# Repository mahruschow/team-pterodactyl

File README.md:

# Team PTERODACTYL

Working files for the UMD near-space PTERODACTYL sensor-board redesign. The current board is an imported **v3.8 v11 baseline**, not a completed next-launch design or a fabrication release.

## Team handoff and planning

For a quick picture of progress and what's left, read [docs/REMAINING_WORK.md](docs/REMAINING_WORK.md). Start with [docs/README.md](docs/README.md) for the shared planning directory, then [current status and resume steps](docs/CURRENT_STATUS.md). The directory includes requirements, the development plan, session notes, the supplied parts workbook and native KiCad validation evidence so teammates can continue without the previous chat.

Step 3 now includes a project-local `Pterodactyl_Modules` library with draft BNO055 #2472/MS8607 #4716 carrier footprints with matching symbols, a Teensy SSW carrier, and an unassigned GPS #5440 logical symbol, plus documented connector/mounting proposals. They are not assigned to the main circuit. See [the footprint review](docs/FOOTPRINT_REVIEW.md) for pin mapping, validation and outstanding physical-fit requirements.

Step 5 adds a separate **draft v4 schematic** in `Native_KiCad_v4/`, built from the documented connection map and power architecture. It passes ERC with 0 violations and matches an independent net list, but it is not yet team-reviewed. Step 7 adds a placed (not yet routed) v4 PCB in the same project; see [the draft layout](docs/PCB_LAYOUT_V4.md). See [the power architecture and schematic plan](docs/POWER_ARCHITECTURE.md).

## Open the design

Use KiCad 10 to open `Native_KiCad_v11/PTERODACTYL_v3.8_v11.kicad_pro`. The project contains a native KiCad schematic, PCB, imported symbol and footprint libraries, and project-local library tables. These files were converted from the supplied Autodesk Fusion/Eagle source; component choices and connectivity still need engineering review.

| Folder or file | Purpose |
|---|---|
| `Native_KiCad_v11/` | Editable KiCad project and the saved October 7, 2026 PCB DRC report |
| `Native_KiCad_v4/` | Draft v4 project: schematic (Step 5) and placed, unrouted PCB (Step 7); see docs/PCB_LAYOUT_V4.md |
| `KiCad_import/` | Eagle XML schematic and board pair prepared for KiCad's Eagle importer |
| `Original_Fusion_source/` | Supplied editable `.f3z`, `.sch`, and `.brd` files for comparison |
| `Firmware_v4/` | Draft v4 logger firmware (Step 6); compiles for Teensy 4.1, not yet hardware-tested |
| `Firmware_reference/` | Original v19 and v19.1 firmware archives from the supplied package; not validated for this redesign |
| `Reference_Gerbers_v12_DO_NOT_ORDER/` | Historical Gerbers for revision comparison only |
| `PTERODACTYL_V3.8_Setup_reference.pdf` | Original setup guide from the supplied package |
| `CUSTOM_BOARD_BRIEF.md` | Sensor goals and decisions still to make |

## Current state

The imported PCB has approximately 97.79 × 97.79 mm outer dimensions, four copper layers, 39 footprints, 417 tracks, and two refilled copper zones. It uses a Teensy 4.1 baseline. A fresh KiCad 10.0.7 audit on October 18, 2026 reproduced **11 PCB DRC errors, 428 warnings, and 0 unconnected items**. Schematic ERC reported **33 errors and 10 warnings**, with **52 additional schematic/PCB parity warnings**. These findings remain unresolved. See the [validation report](docs/validation/2026-10-18/VALIDATION_SUMMARY.md) for triage and check limitations, and the [development plan](docs/DEVELOPMENT_PLAN.md) for next steps. The symbols, pin mapping, power architecture and exact module footprints still require engineering review.

The supplied Gerbers say v3.8 **v12** while the editable Fusion source says v3.8 **v11**; the Gerber job metadata also contains a v3.7 identifier. Reconcile those revisions before using any prior files for fabrication.

## Next-launch work

The intended board should log gyroscope, accelerometer, orientation, GPS, pressure, humidity, temperature, and derived altitude data. The working selection is Teensy 4.1 with Adafruit BNO055 2472, MS8607 4716 and PA1616D GPS 5440. The lead has specified no telemetry: record onboard to microSD for analysis after recovery. Saadat selected the core logger with power control, status LEDs and supply monitoring; OLED, remote probes, alternative IMU, heater and servos are outside this scope. Component placement must address interference. Battery/runtime, quantitative performance, enclosure/environment, exact control workflow and manufacturer constraints remain open. See `CUSTOM_BOARD_BRIEF.md` and the [version-one requirements draft](docs/V1_REQUIREMENTS.md), which distinguishes the selected baseline from proposed behavior and open decisions.

Before fabrication: agree on the requirements and reference revision; review the schematic and all footprints against component datasheets; check power, pin mapping, routing, and board dimensions; resolve DRC/ERC failures; generate fresh Gerbers and drill files from the approved KiCad board; inspect them in a Gerber viewer; and obtain a hardware review and prototype test.

## Collaborating

Clone this private repository, open the `.kicad_pro` file, and commit changes on a branch. Keep the KiCad project, schematic, PCB, and local libraries together. Do not commit editor lock files or local UI settings. Explain changes to connectors, sensors, pin mapping, and power in the commit or pull request so they can be checked against the schematic and firmware.

**Do not send the reference Gerbers or this imported baseline directly to a manufacturer.**

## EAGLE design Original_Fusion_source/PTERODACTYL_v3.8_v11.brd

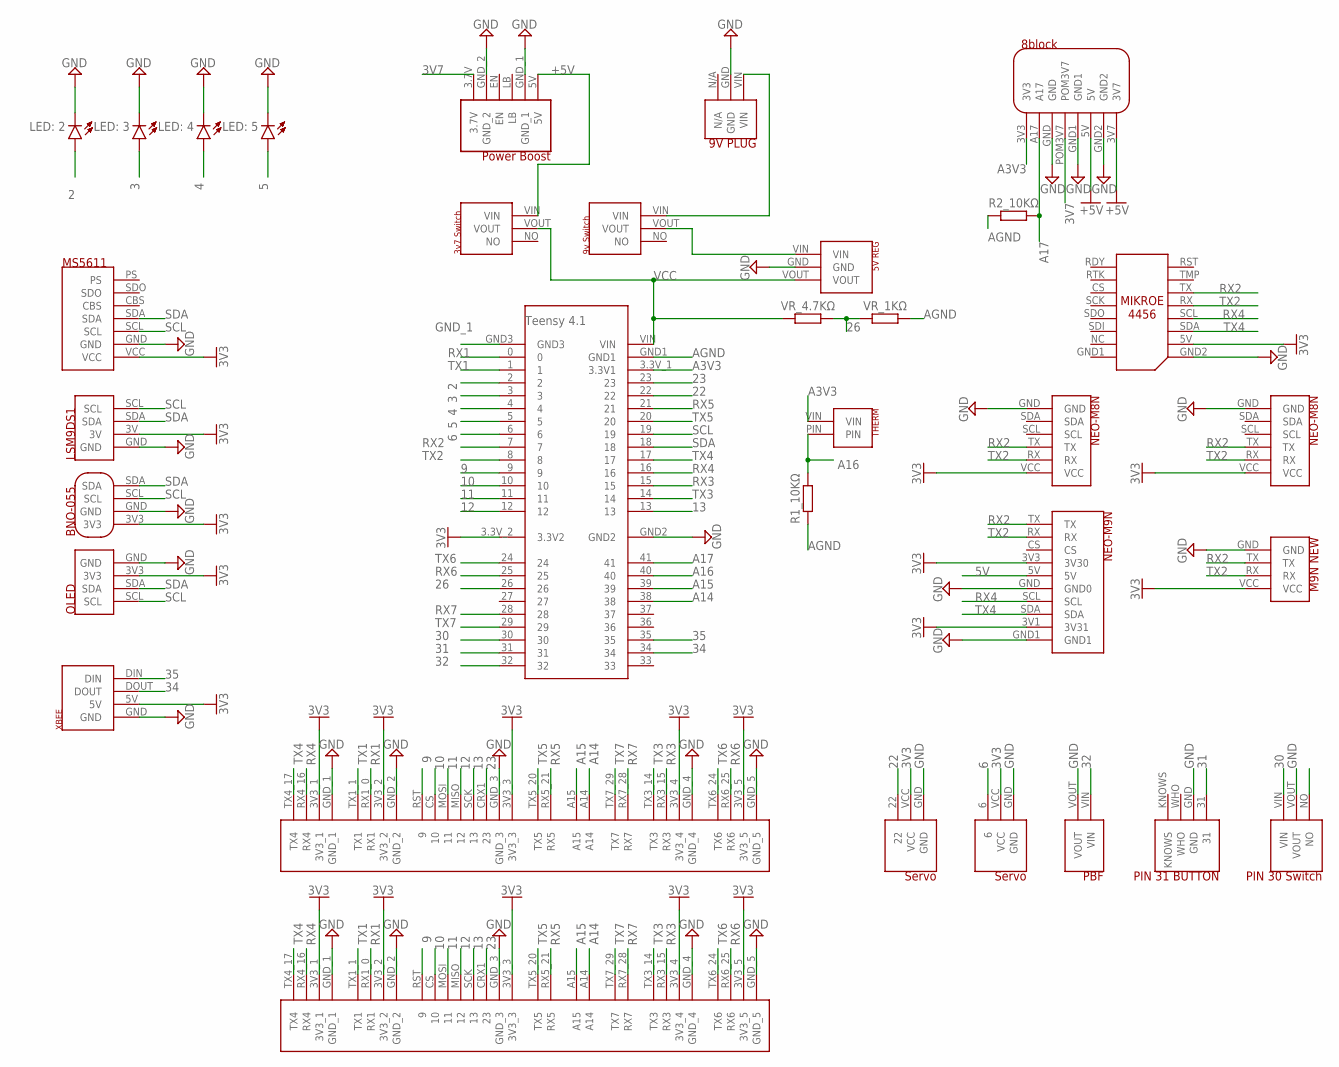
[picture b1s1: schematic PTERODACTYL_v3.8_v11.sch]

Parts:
D1: LED: 3; LEDRD254W60D565H860B_W
D2: LED: 4; LEDRD254W60D565H860B
D3: LED: 5; LEDRD254W60D565H860B_B
D4: LED: 2; LEDRD254W60D565H860B_Y
R1_10KΩ, R2_10KΩ: R_AXIAL-11.7MM-PITCH; RESAD1176W63L850D250B
U$1: FEMALE_HEADERS_V1.3
U$2: TERMINAL_BLOCK_V1.3
U$3: TEENSY41_SIMPLE
U$4: PT8BLOCK; PTERODACTYL8BLOCK
U$5: 5VREG
U$6: 3V7SWITCH
U$7: 9VSWITCH
U$8: 9VPLUG
U$9: OLED_SIMPLE
U$10: LSM9DS1_SIMPLE
U$11: MS5611
U$12: UBLOXM8NTERMINAL
U$13: UBLOXM8NSIMPLE
U$14: XBEE_SIMPLE
U$15: UBLOXM9NSIMPLE
U$16: THERMISTOR10K1; THERMISTOR10K
U$17: BNO055
U$22: UBLOXM9N_NEW_SIMPLE
U$23: SERVO; PIN6SERVO
U$24: PBF; PULLBEFOREFLIGHT
U$25: BUTTON; PIN31BUTTON
U$26: PIN30SWITCH
U$27: SERVO22; PI22SERVO
U$28: POWERBOOST; 5VPOWERBOOST
U$29: MIKROE
VR_1KΩ, VR_4.7KΩ: R_AXIAL-11.7MM-PITCH; RESAD1176W63L850D250B

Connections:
2: D4.1 (A), U$3.2
3: D1.1 (A), U$3.3
3V3: U$1.3V3_1, U$1.3V3_2, U$1.3V3_3, U$1.3V3_4, U$1.3V3_5, U$2.3V3_1, U$2.3V3_2, U$2.3V3_3, U$2.3V3_4, U$2.3V3_5, U$3.3.3V_2 (3.3V2), U$9.3V3, U$10.3V, U$11.VCC, U$12.VCC, U$13.VCC, U$14.5V, U$15.3V1 (3V31), U$15.3V3 (3V30), U$17.3V3, U$22.VCC, U$23.VCC, U$27.VCC, U$29.5V
3V7: U$4.POM3V7, U$28.3.7V
4: D2.1 (A), U$3.4
5: D3.1 (A), U$3.5
5V: U$15.5V
6: U$3.6, U$23.6
9: U$1.RST (9), U$2.RST (9), U$3.9
10: U$1.CS (10), U$2.CS (10), U$3.10
11: U$1.MOSI (11), U$2.MOSI (11), U$3.11
12: U$1.MISO (12), U$2.MISO (12), U$3.12
13: U$1.SCK (13), U$2.SCK (13), U$3.13
22: U$3.22, U$27.22
23: U$1.CRX1 (23), U$2.CRX1 (23), U$3.23
26: U$3.26, VR_1KΩ.1, VR_4.7KΩ.2
30: U$3.30, U$26.VIN
31: U$3.31, U$25.31
32: U$3.32, U$24.VIN
34: U$3.34, U$14.DOUT
35: U$3.35, U$14.DIN
+5V: U$4.3V7, U$4.5V, U$6.VIN, U$28.5V
A3V3: U$3.3.3V_1 (3.3V1), U$4.3V3, U$16.VIN
A14: U$1.A14, U$2.A14, U$3.38
A15: U$1.A15, U$2.A15, U$3.39
A16: R1_10KΩ.2, U$3.40, U$16.PIN
A17: R2_10KΩ.2, U$3.41, U$4.A17
AGND: R1_10KΩ.1, R2_10KΩ.1, U$3.GND1, VR_1KΩ.2
GND: D1.2 (C), D2.2 (C), D3.2 (C), D4.2 (C), U$1.GND_1, U$1.GND_2, U$1.GND_3, U$1.GND_4, U$1.GND_5, U$2.GND_1, U$2.GND_2, U$2.GND_3, U$2.GND_4, U$2.GND_5, U$3.GND2, U$4.GND, U$4.GND1, U$4.GND2, U$5.GND, U$8.GND, U$9.GND, U$10.GND, U$11.GND, U$12.GND, U$13.GND, U$14.GND, U$15.GND (GND0), U$15.GND1, U$17.GND, U$22.GND, U$23.GND, U$24.VOUT, U$25.GND, U$26.VOUT, U$27.GND, U$28.GND_1, U$28.GND_2, U$29.GND2
GND_1: U$3.GND3
RX1: U$1.RX1_0 (RX1), U$2.RX1_0 (RX1), U$3.0
RX2: U$3.7, U$12.TX, U$13.TX, U$15.TX, U$22.TX, U$29.TX
RX3: U$1.RX3_15 (RX3), U$2.RX3_15 (RX3), U$3.15
RX4: U$1.RX4_16 (RX4), U$2.RX4_16 (RX4), U$3.16, U$15.SCL, U$29.SCL
RX5: U$1.RX5_21 (RX5), U$2.RX5_21 (RX5), U$3.21
RX6: U$1.RX6_25 (RX6), U$2.RX6_25 (RX6), U$3.25
RX7: U$1.RX7_28 (RX7), U$2.RX7_28 (RX7), U$3.28
SCL: U$3.19, U$9.SCL, U$10.SCL, U$11.SCL, U$17.SCL
SDA: U$3.18, U$9.SDA, U$10.SDA, U$11.SDA, U$17.SDA
TX1: U$1.TX1_1 (TX1), U$2.TX1_1 (TX1), U$3.1
TX2: U$3.8, U$12.RX, U$13.RX, U$15.RX, U$22.RX, U$29.RX
TX3: U$1.TX3_14 (TX3), U$2.TX3_14 (TX3), U$3.14
TX4: U$1.TX4_17 (TX4), U$2.TX4_17 (TX4), U$3.17, U$15.SDA, U$29.SDA
TX5: U$1.TX5_20 (TX5), U$2.TX5_20 (TX5), U$3.20
TX6: U$1.TX6_24 (TX6), U$2.TX6_24 (TX6), U$3.24
TX7: U$1.TX7_29 (TX7), U$2.TX7_29 (TX7), U$3.29
VCC: U$3.VIN, U$5.VOUT, U$6.VOUT, VR_4.7KΩ.1
VCC_2: U$7.VIN, U$8.VIN
VCC_3: U$5.VIN, U$7.VOUT

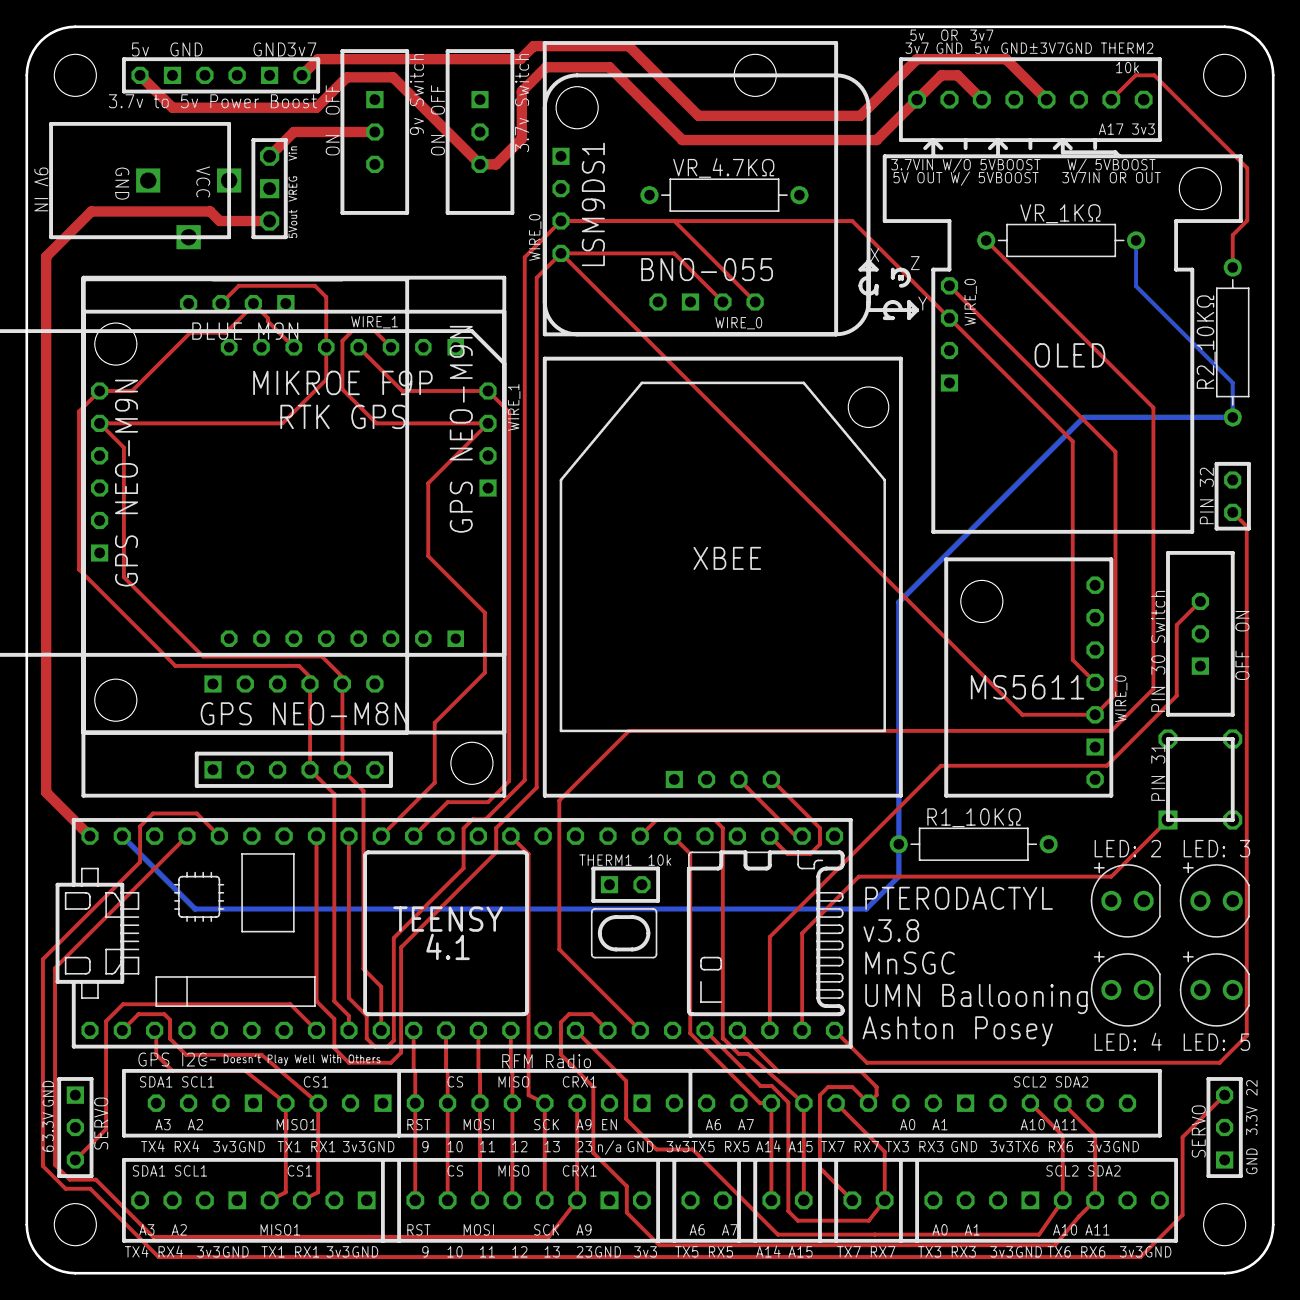
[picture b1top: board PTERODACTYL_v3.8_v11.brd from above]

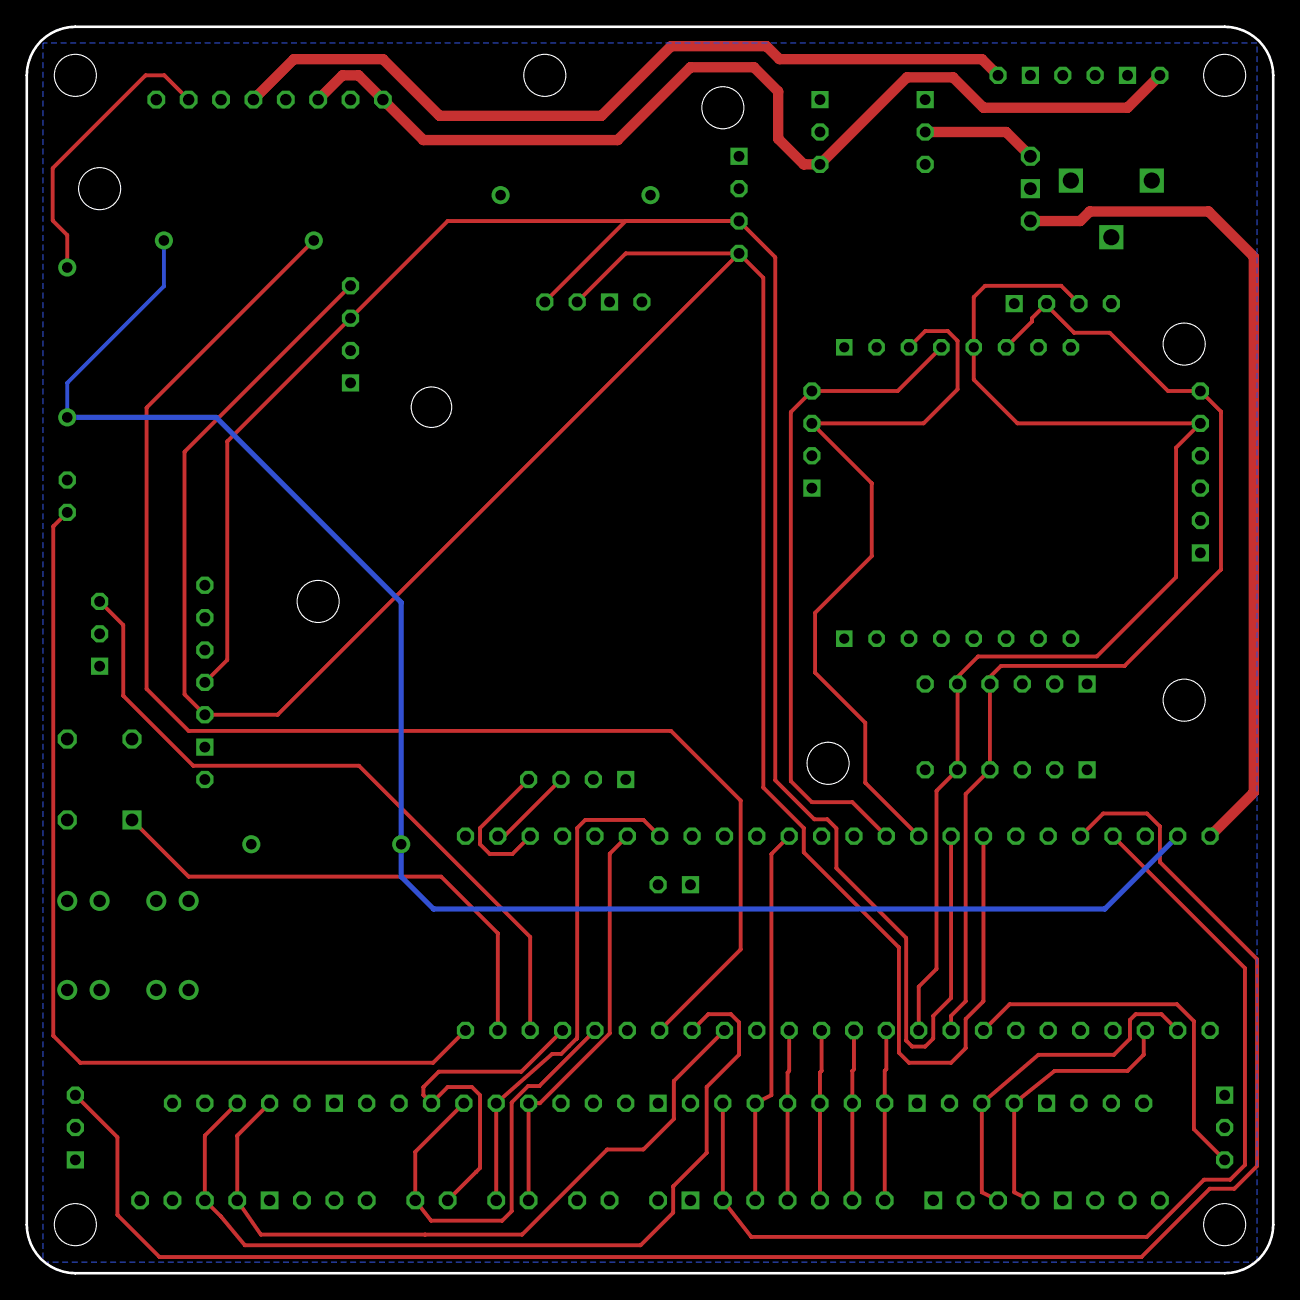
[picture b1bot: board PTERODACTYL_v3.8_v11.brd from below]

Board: 4 copper layers, 97.8 x 97.8 mm, 39 parts (4 on the bottom side), 47 nets.

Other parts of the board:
U$18, U$19, U$20, U$21: HOLE
U$30: PTERODACTYLV3.1
U$32: AXIS
